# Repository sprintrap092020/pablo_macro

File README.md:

Hi everyone. I want to introduce you my first ever project. This is macropad(minikeyboard) with mechanical cherry mx switches.

its based on 1x seeed xiao rp2040 12x cherry mx switches 12x 1n4148 diodes(dip) 1x ec11 encoder and 12x sk6812mini-e adress leds and one 330 ohm resistor(0.25w) 

also i made case for that stuff in fusion so you can use itwithout any problems
all of them are called pablo_macro_case

pablo_macro_case is main case 

pablo_macro_case_lid is lid for that case
in summary case is 117x77x19mm (raw case without switches and keycaps)

to assemble this whole thing you need to obtain pcb case case lid and all components from above
also you will need soldering iron and flux to make stable connections beetwen components and pcb

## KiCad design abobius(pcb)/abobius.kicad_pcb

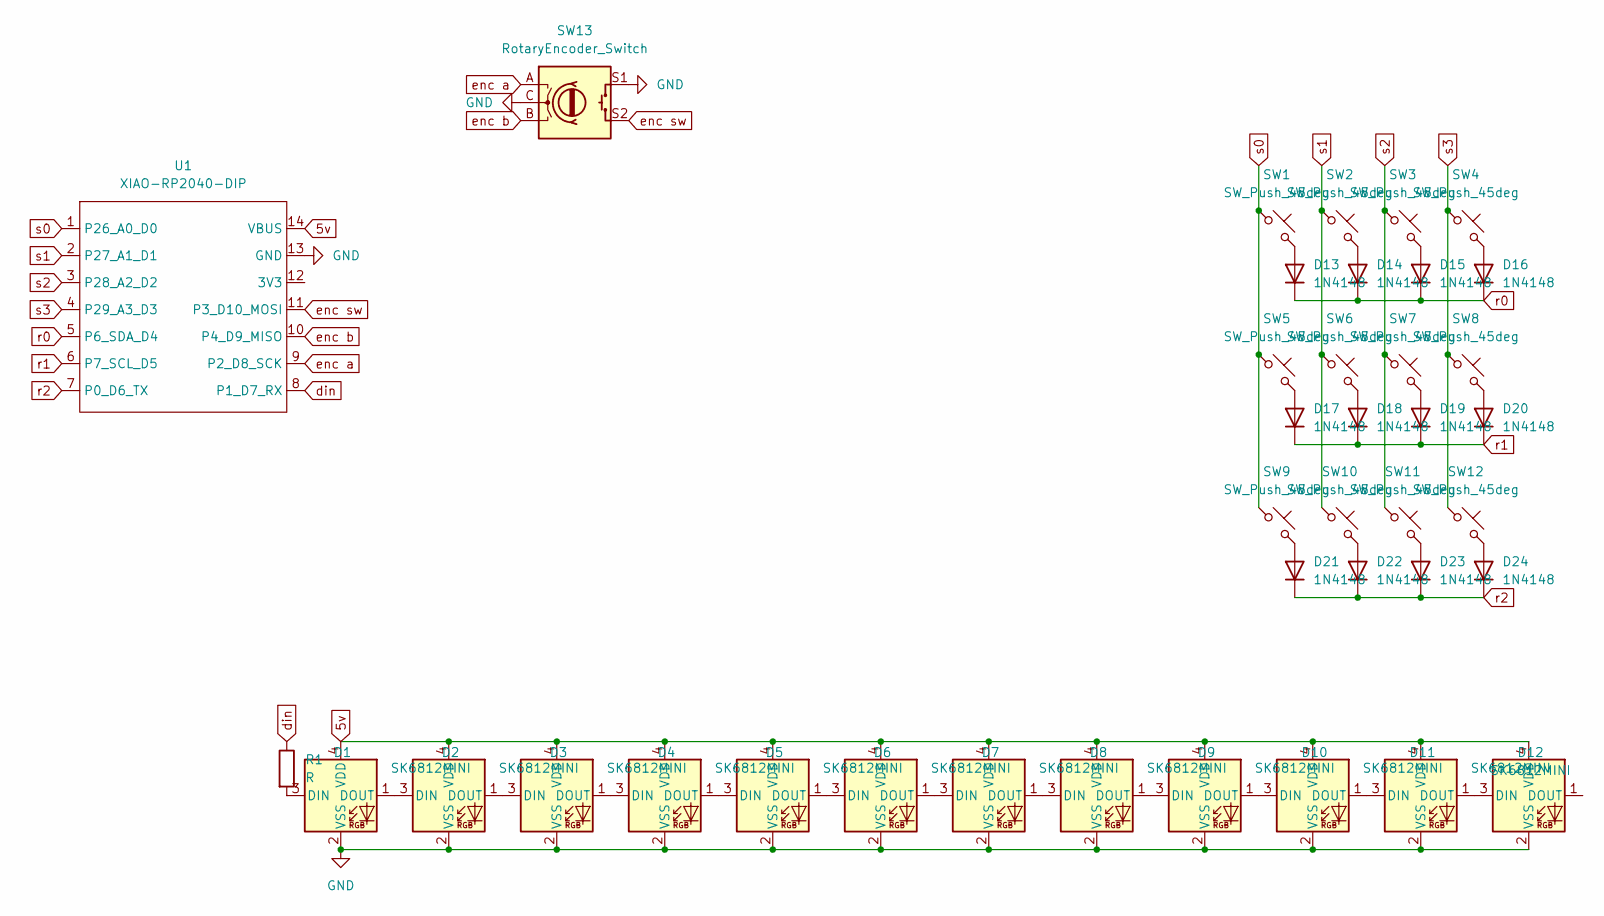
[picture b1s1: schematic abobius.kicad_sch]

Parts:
D1, D2, D3, D4, D5, D6, D7, D8, D9, D10, D11, D12: SK6812MINI; LED_SK6812MINI_PLCC4_3.5x3.5mm_P1.75mm
D13, D14, D15, D16, D17, D18, D19, D20, D21, D22, D23, D24: 1N4148; D_DO-35_SOD27_P7.62mm_Horizontal
R1: R; R_Axial_DIN0207_L6.3mm_D2.5mm_P7.62mm_Horizontal
SW1, SW2, SW3, SW4, SW5, SW6, SW7, SW8, SW9, SW10, SW11, SW12: SW_Push_45deg; SW_Cherry_MX_1.00u_PCB
SW13: RotaryEncoder_Switch; RotaryEncoder_Alps_EC11E-Switch_Vertical_H20mm
U1: XIAO-RP2040-DIP; Seeed_XIAO_RP2040

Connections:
5v: D1.4 (VDD), D2.4 (VDD), D3.4 (VDD), D4.4 (VDD), D5.4 (VDD), D6.4 (VDD), D7.4 (VDD), D8.4 (VDD), D9.4 (VDD), D10.4 (VDD), D11.4 (VDD), D12.4 (VDD), U1.14 (VBUS)
GND: D1.2 (VSS), D2.2 (VSS), D3.2 (VSS), D4.2 (VSS), D5.2 (VSS), D6.2 (VSS), D7.2 (VSS), D8.2 (VSS), D9.2 (VSS), D10.2 (VSS), D11.2 (VSS), D12.2 (VSS), SW13.C, SW13.S1, U1.13 (GND)
unnamed: D1.3 (DIN), R1.2
unnamed: D1.1 (DOUT), D2.3 (DIN)
unnamed: D2.1 (DOUT), D3.3 (DIN)
unnamed: D3.1 (DOUT), D4.3 (DIN)
unnamed: D4.1 (DOUT), D5.3 (DIN)
unnamed: D5.1 (DOUT), D6.3 (DIN)
unnamed: D6.1 (DOUT), D7.3 (DIN)
unnamed: D7.1 (DOUT), D8.3 (DIN)
unnamed: D8.1 (DOUT), D9.3 (DIN)
unnamed: D9.1 (DOUT), D10.3 (DIN)
unnamed: D10.1 (DOUT), D11.3 (DIN)
unnamed: D11.1 (DOUT), D12.3 (DIN)
unnamed: D13.2 (A), SW1.2
unnamed: D14.2 (A), SW2.2
unnamed: D15.2 (A), SW3.2
unnamed: D16.2 (A), SW4.2
unnamed: D17.2 (A), SW5.2
unnamed: D18.2 (A), SW6.2
unnamed: D19.2 (A), SW7.2
unnamed: D20.2 (A), SW8.2
unnamed: D21.2 (A), SW9.2
unnamed: D22.2 (A), SW10.2
unnamed: D23.2 (A), SW11.2
unnamed: D24.2 (A), SW12.2
din: R1.1, U1.8 (P1_D7_RX)
enc a: SW13.A, U1.9 (P2_D8_SCK)
enc b: SW13.B, U1.10 (P4_D9_MISO)
enc sw: SW13.S2, U1.11 (P3_D10_MOSI)
r0: D13.1 (K), D14.1 (K), D15.1 (K), D16.1 (K), U1.5 (P6_SDA_D4)
r1: D17.1 (K), D18.1 (K), D19.1 (K), D20.1 (K), U1.6 (P7_SCL_D5)
r2: D21.1 (K), D22.1 (K), D23.1 (K), D24.1 (K), U1.7 (P0_D6_TX)
s0: SW1.1, SW5.1, SW9.1, U1.1 (P26_A0_D0)
s1: SW2.1, SW6.1, SW10.1, U1.2 (P27_A1_D1)
s2: SW3.1, SW7.1, SW11.1, U1.3 (P28_A2_D2)
s3: SW4.1, SW8.1, SW12.1, U1.4 (P29_A3_D3)

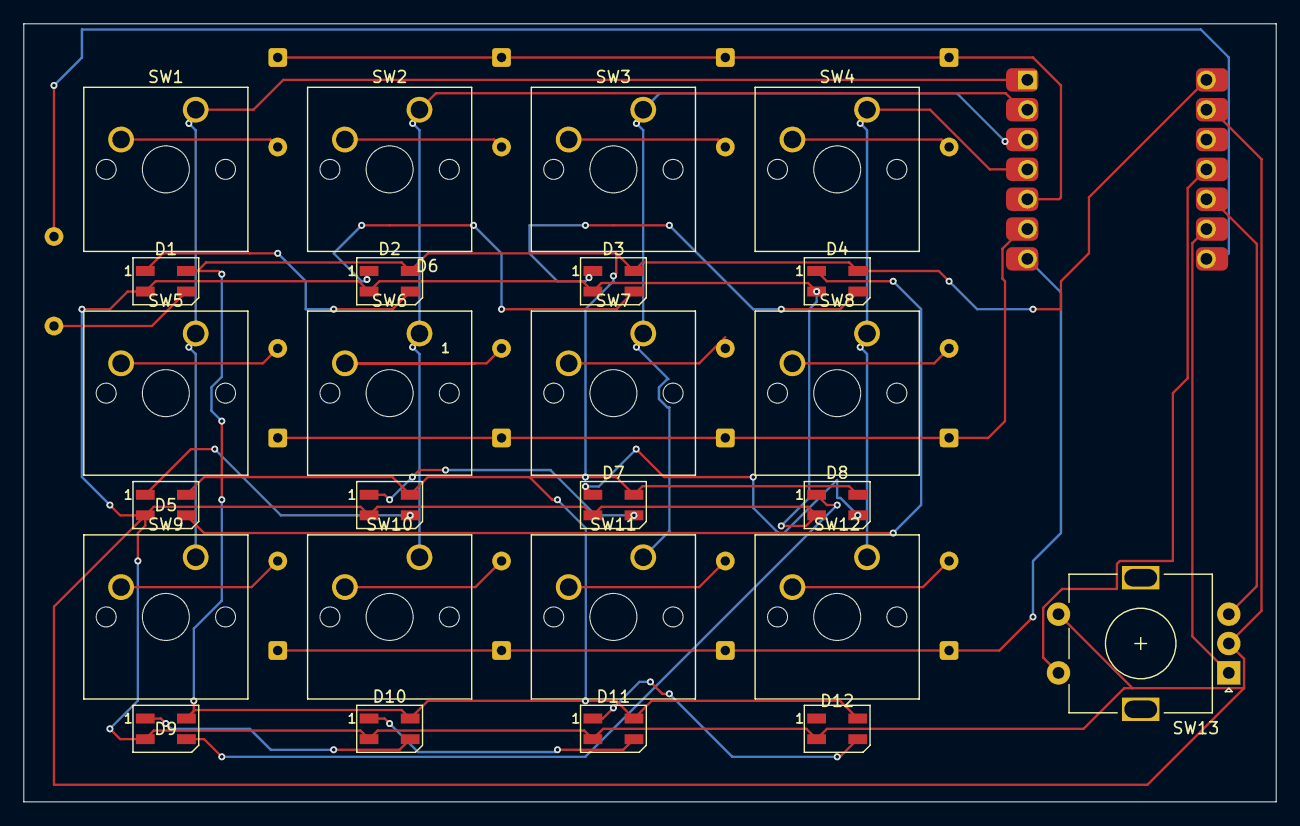
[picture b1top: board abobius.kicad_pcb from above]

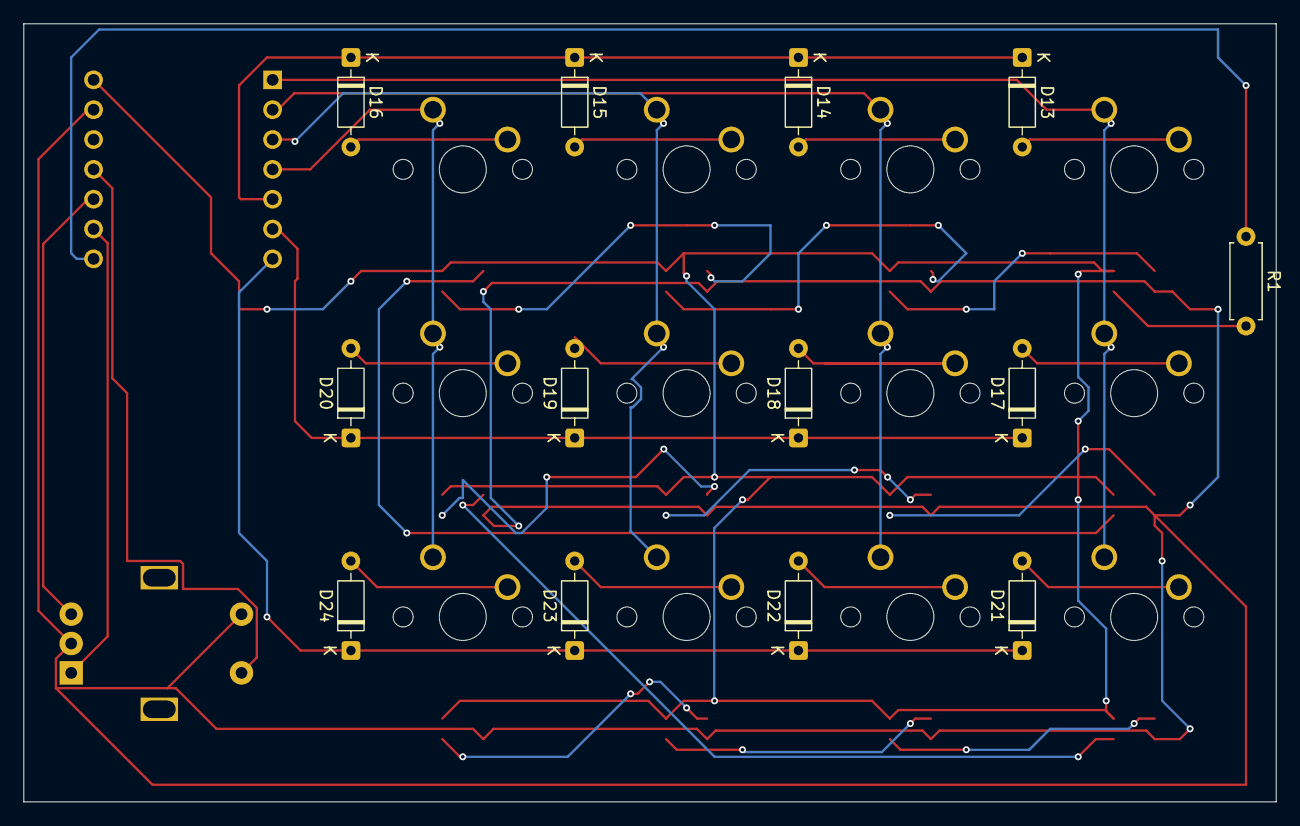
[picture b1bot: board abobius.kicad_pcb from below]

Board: 2 copper layers, 106.6 x 66.2 mm, 39 parts (13 on the bottom side), 37 nets.

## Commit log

2026-03-05 Add project introduction for macropad
    Introduced project details for macropad with components and case information.
2026-03-05 Update README with case dimensions and assembly info
    Added summary dimensions and assembly requirements.
